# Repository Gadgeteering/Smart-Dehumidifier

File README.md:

# Smart-Dehumidifier

This project modifies a Demuidifier into a Smart Dehumidifier so that it is automatically turned on when it is predicted that condensation will form on a window pane.

More details of project are available here

https://www.instructables.com/id/Dehumidifier/

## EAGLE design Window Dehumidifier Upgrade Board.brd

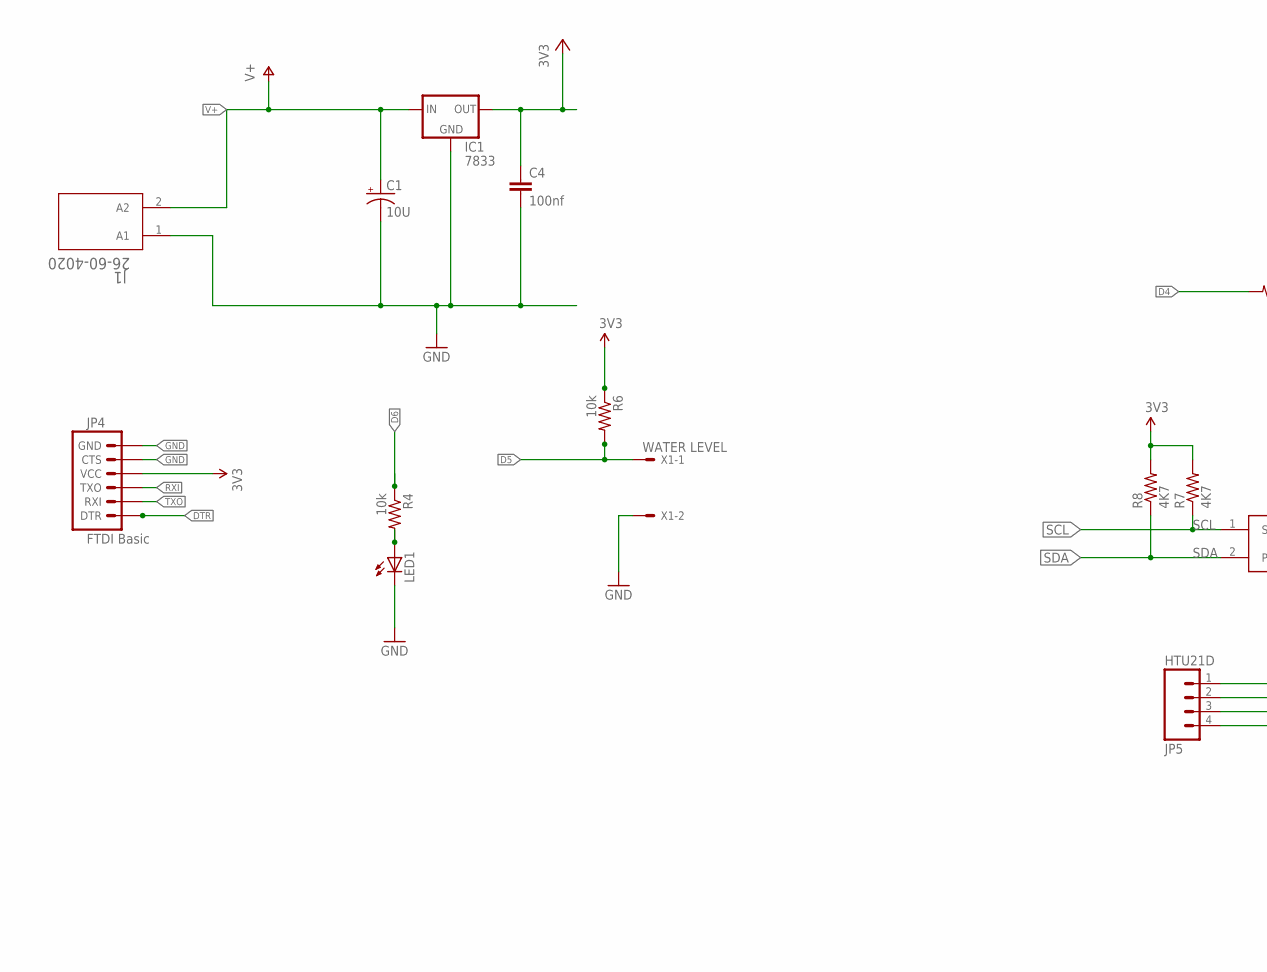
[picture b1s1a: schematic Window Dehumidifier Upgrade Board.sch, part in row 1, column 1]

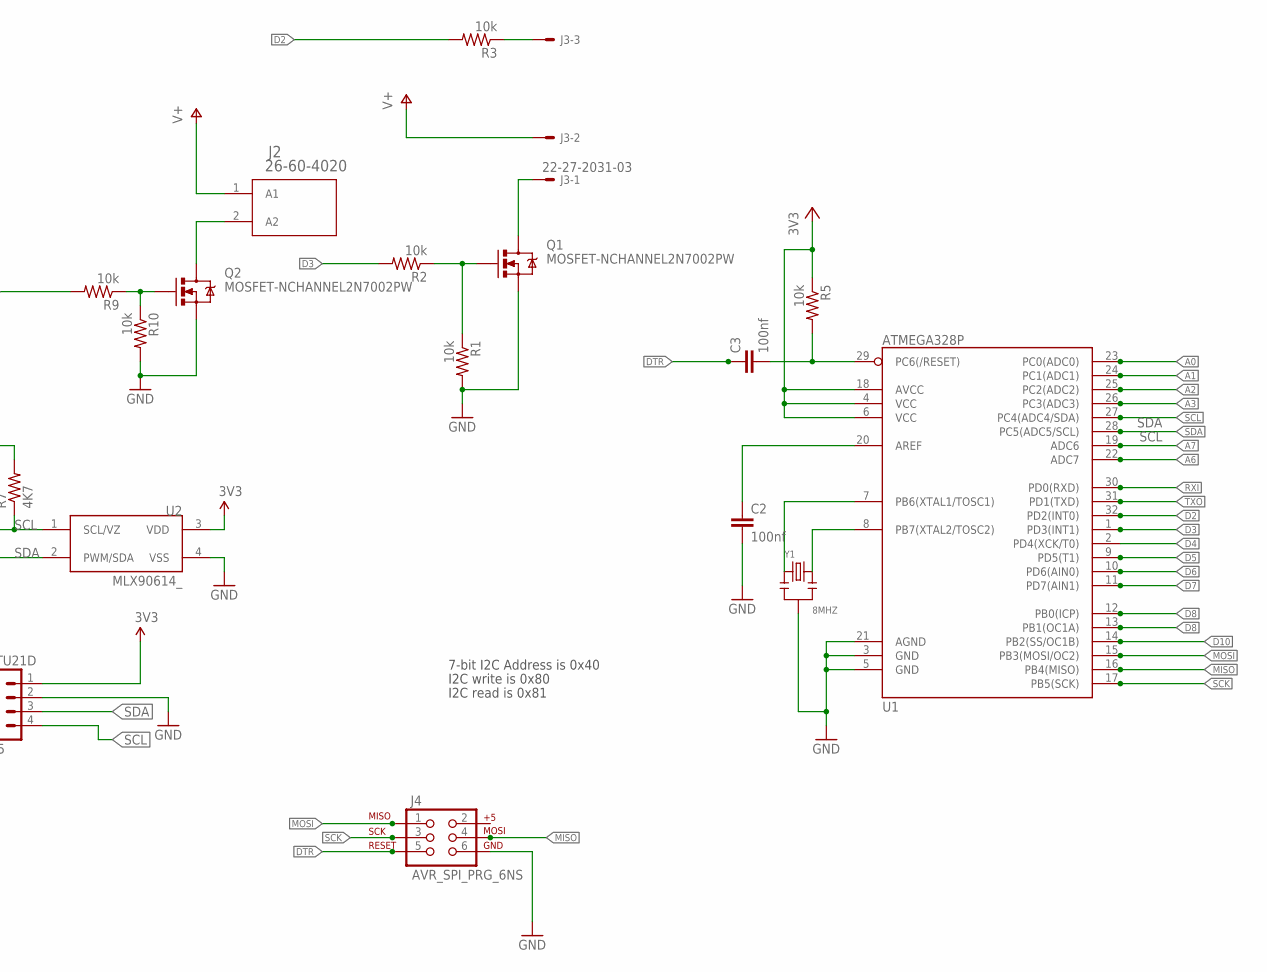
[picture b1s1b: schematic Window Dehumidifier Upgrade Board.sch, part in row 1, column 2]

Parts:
C1: 10U; CPOL-RADIAL-100UF-25V
C2, C3, C4: 100nf; 0805
IC1: 7833; TO-92
J1, J2: 26-60-4020
J3: 22-27-2031-03; 6410-03
J4: AVR_SPI_PRG_6NS; 2X3-NS
JP4: FTDI Basic; 1X06
JP5: HTU21D; 1X04
LED1: LED3MM
Q1, Q2: MOSFET-NCHANNEL2N7002PW; SOT323
R1, R2, R3, R4, R5, R6, R9, R10: 10k; 0805
R7, R8: 4K7; 0805
U1: ATMEGA328P; TQFP32-08
U2: MLX90614_; TO-39
X1: WATER LEVEL; 22-23-2021
Y1: 8MHZ; X3-2.5-8X3X5.5MM

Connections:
3.3V: JP4.4 (VCC)
3V3: C4.1, IC1.3 (OUT), JP5.1, R5.1, R6.1, R7.2, R8.2, U1.4 (VCC), U1.6 (VCC), U1.18 (AVCC), U2.3 (VDD)
A0: U1.23 (PC0(ADC0))
A1: U1.24 (PC1(ADC1))
A2: U1.25 (PC2(ADC2))
A3: U1.26 (PC3(ADC3))
A6: U1.22 (ADC7)
A7: U1.19 (ADC6)
D2: R3.2, U1.32 (PD2(INT0))
D3: R2.2, U1.1 (PD3(INT1))
D4: R9.2, U1.2 (PD4(XCK/T0))
D5: R6.2, U1.9 (PD5(T1)), X1.1
D6: R4.1, U1.10 (PD6(AIN0))
D7: U1.11 (PD7(AIN1))
D8: U1.12 (PB0(ICP))
D9: U1.13 (PB1(OC1A))
D10: U1.14 (PB2(SS/OC1B))
DTR: C3.1, J4.5, JP4.1 (DTR)
GND: C1.2 (-), C2.2, C4.2, IC1.1 (GND), J1.1 (A1), J4.6, JP4.5 (CTS), JP4.6 (GND), JP5.2, LED1.K (C), Q1.2 (S), Q2.2 (S), R1.2, R10.2, U1.3 (GND), U1.5 (GND), U1.21 (AGND), U2.4 (VSS), X1.2, Y1.2
MISO: J4.4, U1.16 (PB4(MISO))
MOSI: J4.1, U1.15 (PB3(MOSI/OC2))
unnamed: Q2.1 (G), R9.1, R10.1
unnamed: J2.2 (A2), Q2.3 (D)
unnamed: Q1.1 (G), R1.1, R2.1
unnamed: J3.1, Q1.3 (D)
unnamed: LED1.A, R4.2
unnamed: J3.3, R3.1
unnamed: C2.1, U1.20 (AREF)
unnamed: C3.2, R5.2, U1.29 (PC6(/RESET))
unnamed: U1.7 (PB6(XTAL1/TOSC1)), Y1.1
unnamed: U1.8 (PB7(XTAL2/TOSC2)), Y1.3
RXI: JP4.3 (TXO), U1.30 (PD0(RXD))
SCK: J4.3, U1.17 (PB5(SCK))
SCL: JP5.4, R7.1, U1.28 (PC5(ADC5/SCL)), U2.1 (SCL/VZ)
SDA: JP5.3, R8.1, U1.27 (PC4(ADC4/SDA)), U2.2 (PWM/SDA)
TXO: JP4.2 (RXI), U1.31 (PD1(TXD))
V+: C1.1 (+), IC1.2 (IN), J1.2 (A2), J2.1 (A1), J3.2

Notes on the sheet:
7-bit I2C Address is 0x40
I2C write is 0x80
I2C read is 0x81

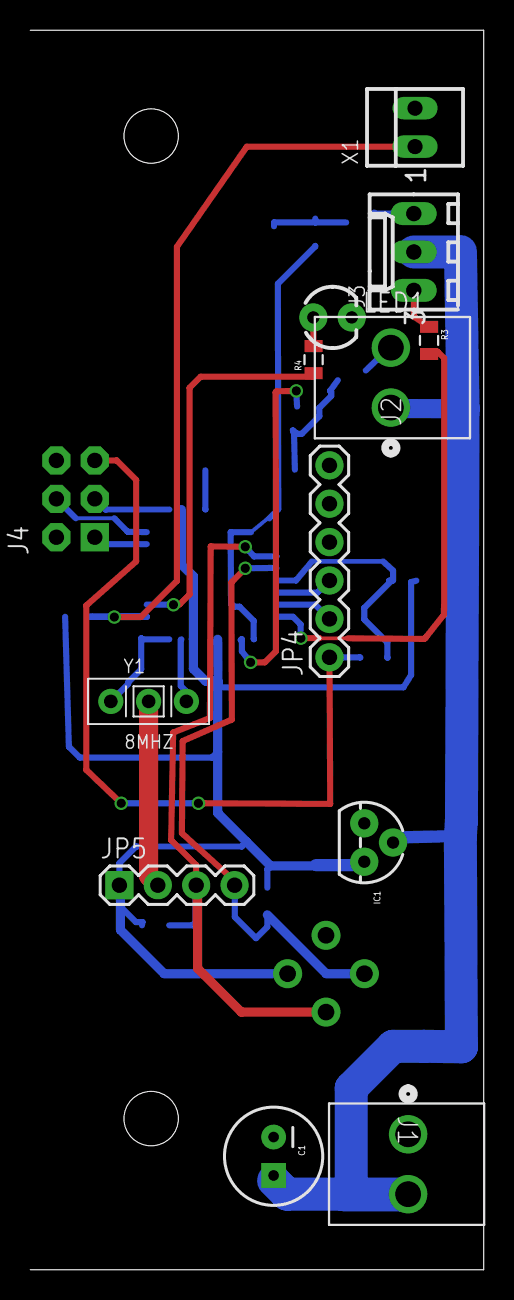
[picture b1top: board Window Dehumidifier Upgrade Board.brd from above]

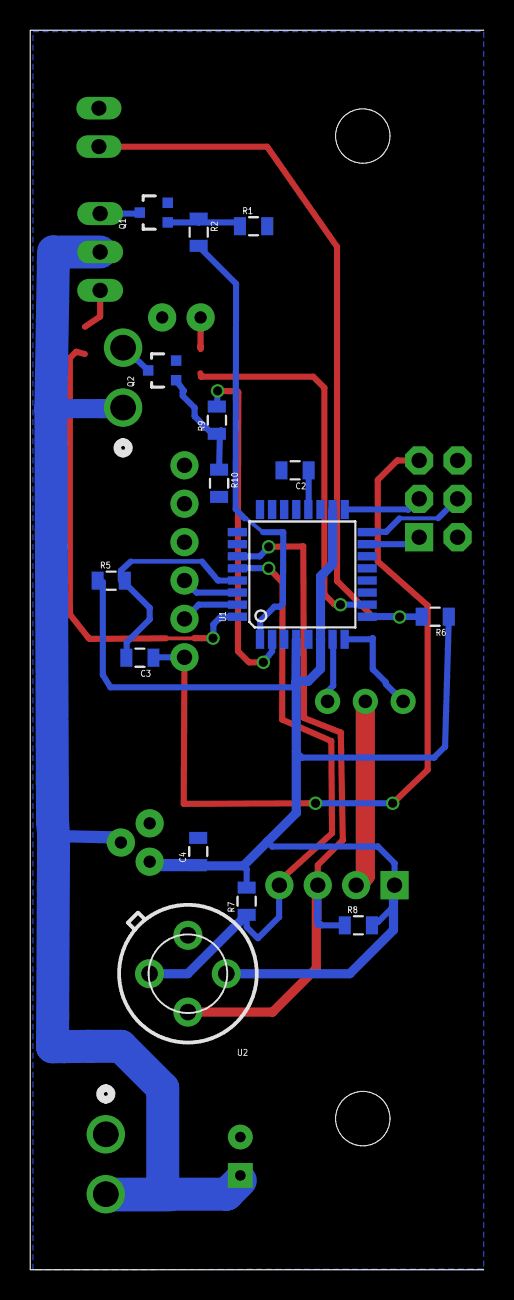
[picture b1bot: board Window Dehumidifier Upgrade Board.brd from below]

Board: 2 copper layers, 30.0 x 82.0 mm, 28 parts (15 on the bottom side), 26 nets.

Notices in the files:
parts and their libraries:
SparkFun-Passives: Licensing: CC v3.0 Share-Alike You are welcome to use this library for commercial purposes.
